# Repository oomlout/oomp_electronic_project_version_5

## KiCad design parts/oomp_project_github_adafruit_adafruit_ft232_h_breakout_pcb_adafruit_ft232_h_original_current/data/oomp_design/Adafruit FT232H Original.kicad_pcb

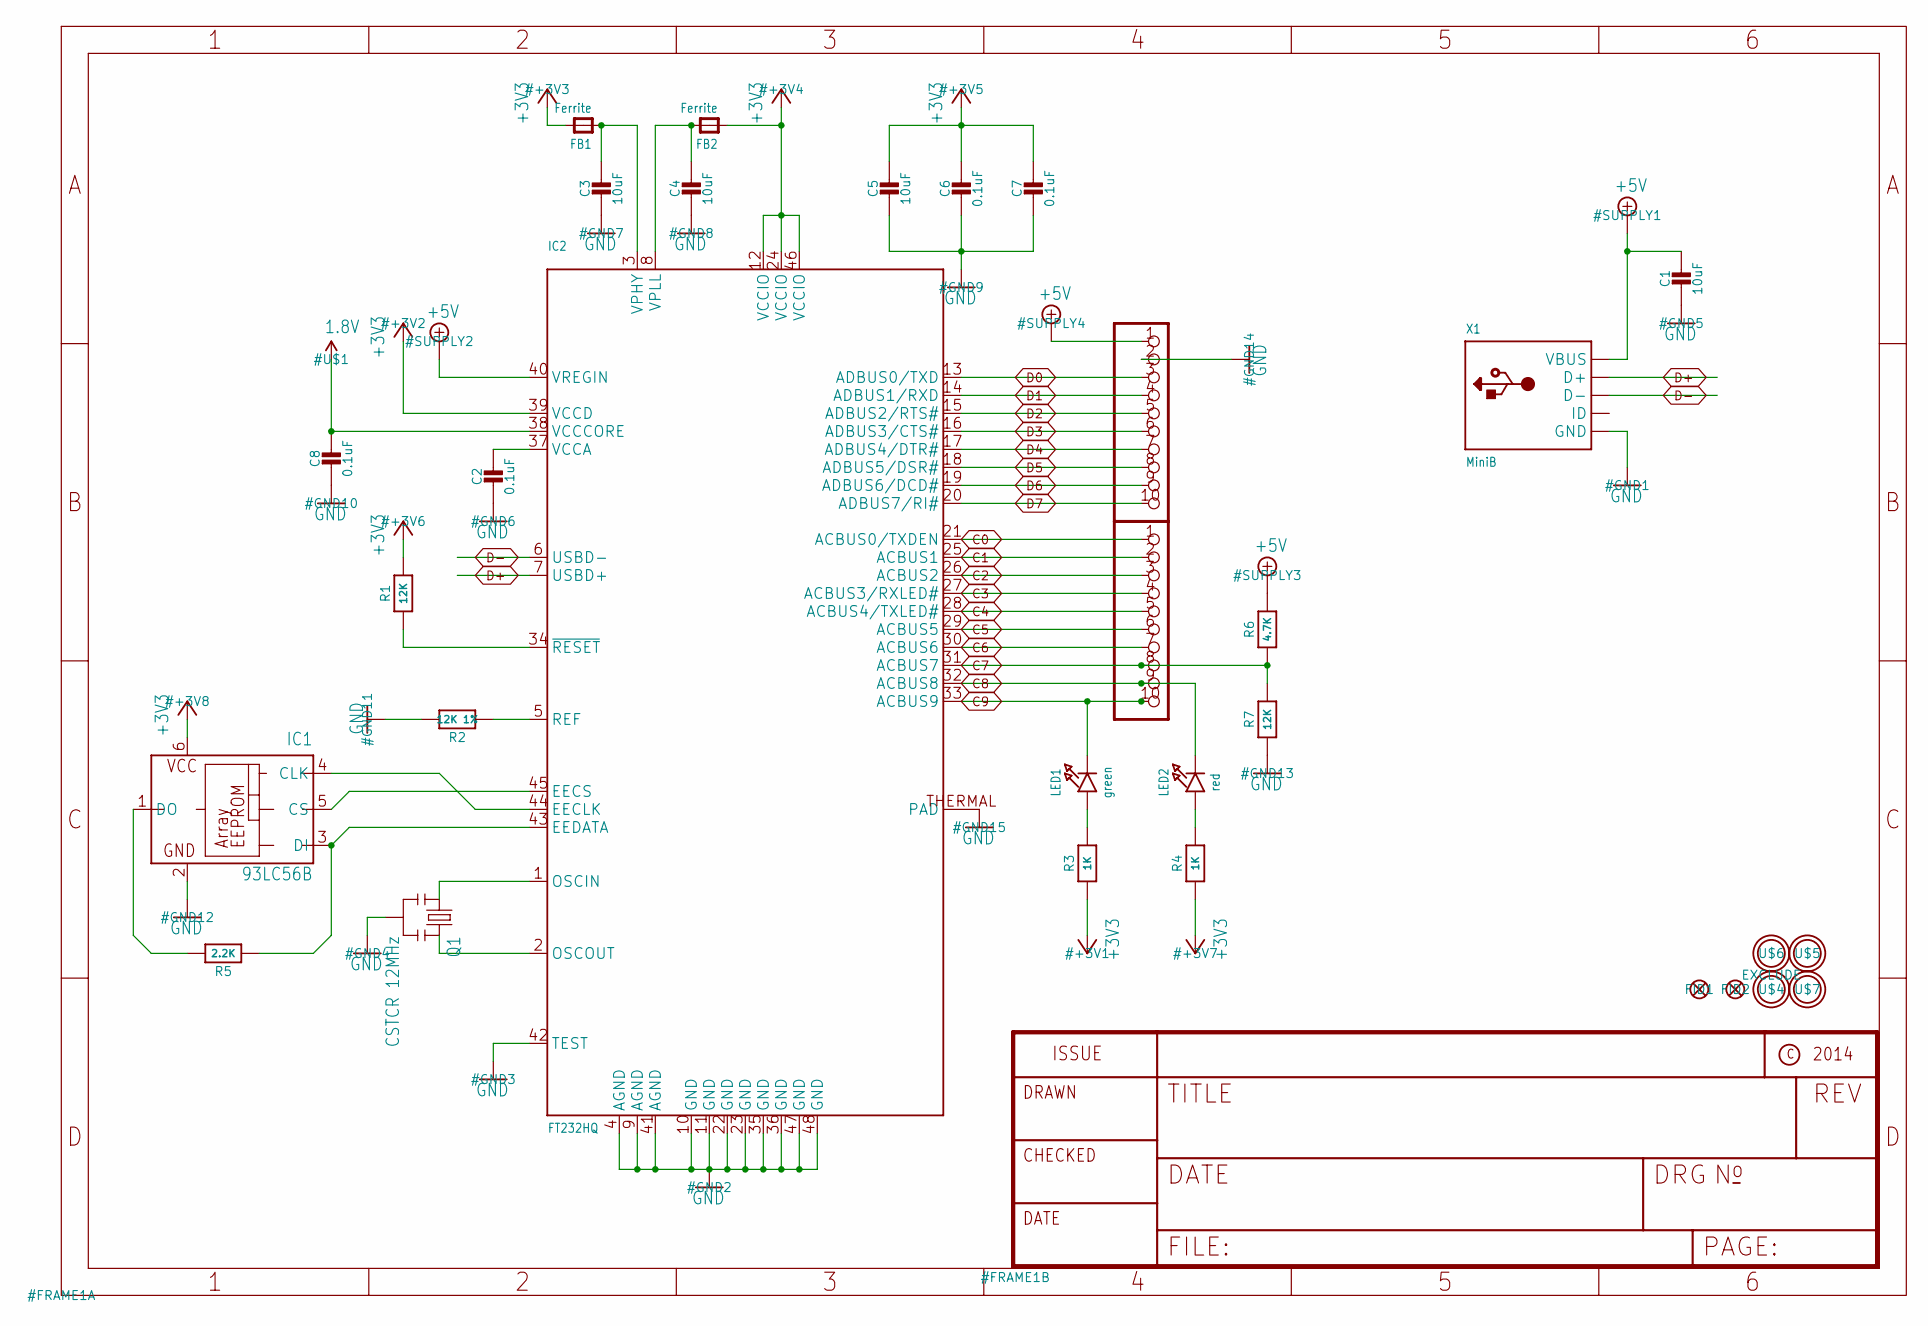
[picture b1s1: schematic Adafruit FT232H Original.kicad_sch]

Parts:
C1, C3, C4, C5: 10uF; 0805-NO
C2, C6, C7, C8: 0.1uF; 0805-NO
FB1, FB2: Ferrite; _0805
FID1, FID2: FIDUCIAL""; FIDUCIAL_1MM
IC1: 93LC56B; SOT23-6; MPN 93LC76AT-I/OT
IC2: FT232HQ; QFN48_8MM
LED1: green; CHIPLED_0805_NOOUTLINE
LED2: red; CHIPLED_0805_NOOUTLINE
Q1: CSTCR 12MHz; RESONATOR-SMD
R1, R7: 12K; 0805-NO
R2: 12K 1%; 0805-NO
R3, R4: 1K; 0805-NO
R5: 2.2K; _0805MP
R6: 4.7K; 0805-NO
U$2, U$3: PINHD-1X10; 1X10-BIG
U$4, U$5, U$6, U$7: MOUNTINGHOLE2.5; MOUNTINGHOLE_2.5_PLATED
X1: MiniB; 4UCONN_20329

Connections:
1.8V: C8.1, IC2.38 (VCCCORE)
+3V3: C5.1, C6.1, C7.1, FB1.2, FB2.1, IC1.6 (VCC), IC2.12 (VCCIO), IC2.24 (VCCIO), IC2.39 (VCCD), IC2.46 (VCCIO), R1.2, R3.1, R4.1
+5V: C1.1, IC2.40 (VREGIN), R6.2, U$2.1, X1.VBUS
C0: IC2.21 (ACBUS0/TXDEN), U$3.1
C1: IC2.25 (ACBUS1), U$3.2
C2: IC2.26 (ACBUS2), U$3.3
C3: IC2.27 (ACBUS3/RXLED#), U$3.4
C4: IC2.28 (ACBUS4/TXLED#), U$3.5
C5: IC2.29 (ACBUS5), U$3.6
C6: IC2.30 (ACBUS6), U$3.7
C7: IC2.31 (ACBUS7), R6.1, R7.2, U$3.8
C8: IC2.32 (ACBUS8), LED2.C, U$3.9
C9: IC2.33 (ACBUS9), LED1.C, U$3.10
D0: IC2.13 (ADBUS0/TXD), U$2.3
D1: IC2.14 (ADBUS1/RXD), U$2.4
D2: IC2.15 (ADBUS2/RTS#), U$2.5
D3: IC2.16 (ADBUS3/CTS#), U$2.6
D4: IC2.17 (ADBUS4/DTR#), U$2.7
D5: IC2.18 (ADBUS5/DSR#), U$2.8
D6: IC2.19 (ADBUS6/DCD#), U$2.9
D7: IC2.20 (ADBUS7/RI#), U$2.10
D+: IC2.7 (USBD+), X1.D+
D-: IC2.6 (USBD-), X1.D-
GND: C1.2, C2.2, C3.2, C4.2, C5.2, C6.2, C7.2, C8.2, IC1.2 (GND), IC2.4 (AGND), IC2.9 (AGND), IC2.10 (GND), IC2.11 (GND), IC2.22 (GND), IC2.23 (GND), IC2.35 (GND), IC2.36 (GND), IC2.41 (AGND), IC2.42 (TEST), IC2.47 (GND), IC2.48 (GND), IC2.THERMAL (PAD), Q1.2, R2.2, R7.1, U$2.2, X1.BASE@1 (GND), X1.BASE@2 (GND), X1.GND, X1.SPRT@1 (GND), X1.SPRT@2 (GND), X1.SPRT@3 (GND), X1.SPRT@4 (GND)
unnamed: IC2.1 (OSCIN), Q1.1
unnamed: IC2.2 (OSCOUT), Q1.3
unnamed: IC2.5 (REF), R2.1
unnamed: LED2.A, R4.2
unnamed: IC2.34 (~RESET), R1.1
unnamed: LED1.A, R3.2
unnamed: IC1.3 (DI), IC2.43 (EEDATA), R5.1
unnamed: IC1.5 (CS), IC2.45 (EECS)
unnamed: IC1.4 (CLK), IC2.44 (EECLK)
unnamed: IC1.1 (DO), R5.2
VCCA: C2.1, IC2.37 (VCCA)
VPHY: C3.1, FB1.1, IC2.3 (VPHY)
VPLL: C4.1, FB2.2, IC2.8 (VPLL)

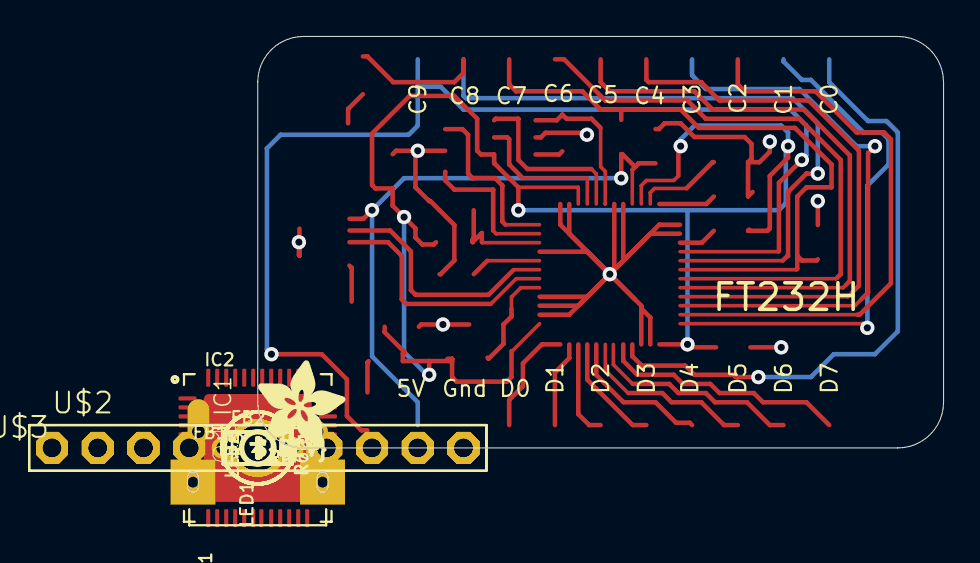
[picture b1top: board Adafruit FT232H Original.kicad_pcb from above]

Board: 2 copper layers, 38.1 x 22.9 mm, 34 parts (1 on the bottom side), 37 nets.

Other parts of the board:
U$8: ADAFRUIT_5MM
U$9: ADAFRUIT_TEXT_30MM
U$11: PCBFEAT-REV-040

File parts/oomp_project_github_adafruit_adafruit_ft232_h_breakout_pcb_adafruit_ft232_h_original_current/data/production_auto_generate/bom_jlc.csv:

Comment,Designator,Footprint,LCSC Part #
,U$8,Adafruit FT232H Original-import-fps:ADAFRUIT_5MM,
,U$9,Adafruit FT232H Original-import-fps:ADAFRUIT_TEXT_30MM,
,U$11,Adafruit FT232H Original-import-fps:PCBFEAT-REV-040,
0.1uF,"C2,C6,C7,C8",Adafruit FT232H Original-import-fps:0805-NO,
10uF,"C1,C3,C4,C5",Adafruit FT232H Original-import-fps:0805-NO,
12K,"R1,R7",Adafruit FT232H Original-import-fps:0805-NO,C2907225
12K 1%,R2,Adafruit FT232H Original-import-fps:0805-NO,C2907225
1K,"R3,R4",Adafruit FT232H Original-import-fps:0805-NO,C17513
2.2K,R5,Adafruit FT232H Original-import-fps:_0805MP,C17520
4.7K,R6,Adafruit FT232H Original-import-fps:0805-NO,C2907264
93LC56B,IC1,Adafruit FT232H Original-import-fps:SOT23-6,
CSTCR 12MHz,Q1,Adafruit FT232H Original-import-fps:RESONATOR-SMD,
Ferrite,"FB1,FB2",Adafruit FT232H Original-import-fps:_0805,
FT232HQ,IC2,Adafruit FT232H Original-import-fps:QFN48_8MM,
green,LED1,Adafruit FT232H Original-import-fps:CHIPLED_0805_NOOUTLINE,
MiniB,X1,Adafruit FT232H Original-import-fps:4UCONN_20329,
PINHD-1X10,"U$2,U$3",Adafruit FT232H Original-import-fps:1X10-BIG,
red,LED2,Adafruit FT232H Original-import-fps:CHIPLED_0805_NOOUTLINE,

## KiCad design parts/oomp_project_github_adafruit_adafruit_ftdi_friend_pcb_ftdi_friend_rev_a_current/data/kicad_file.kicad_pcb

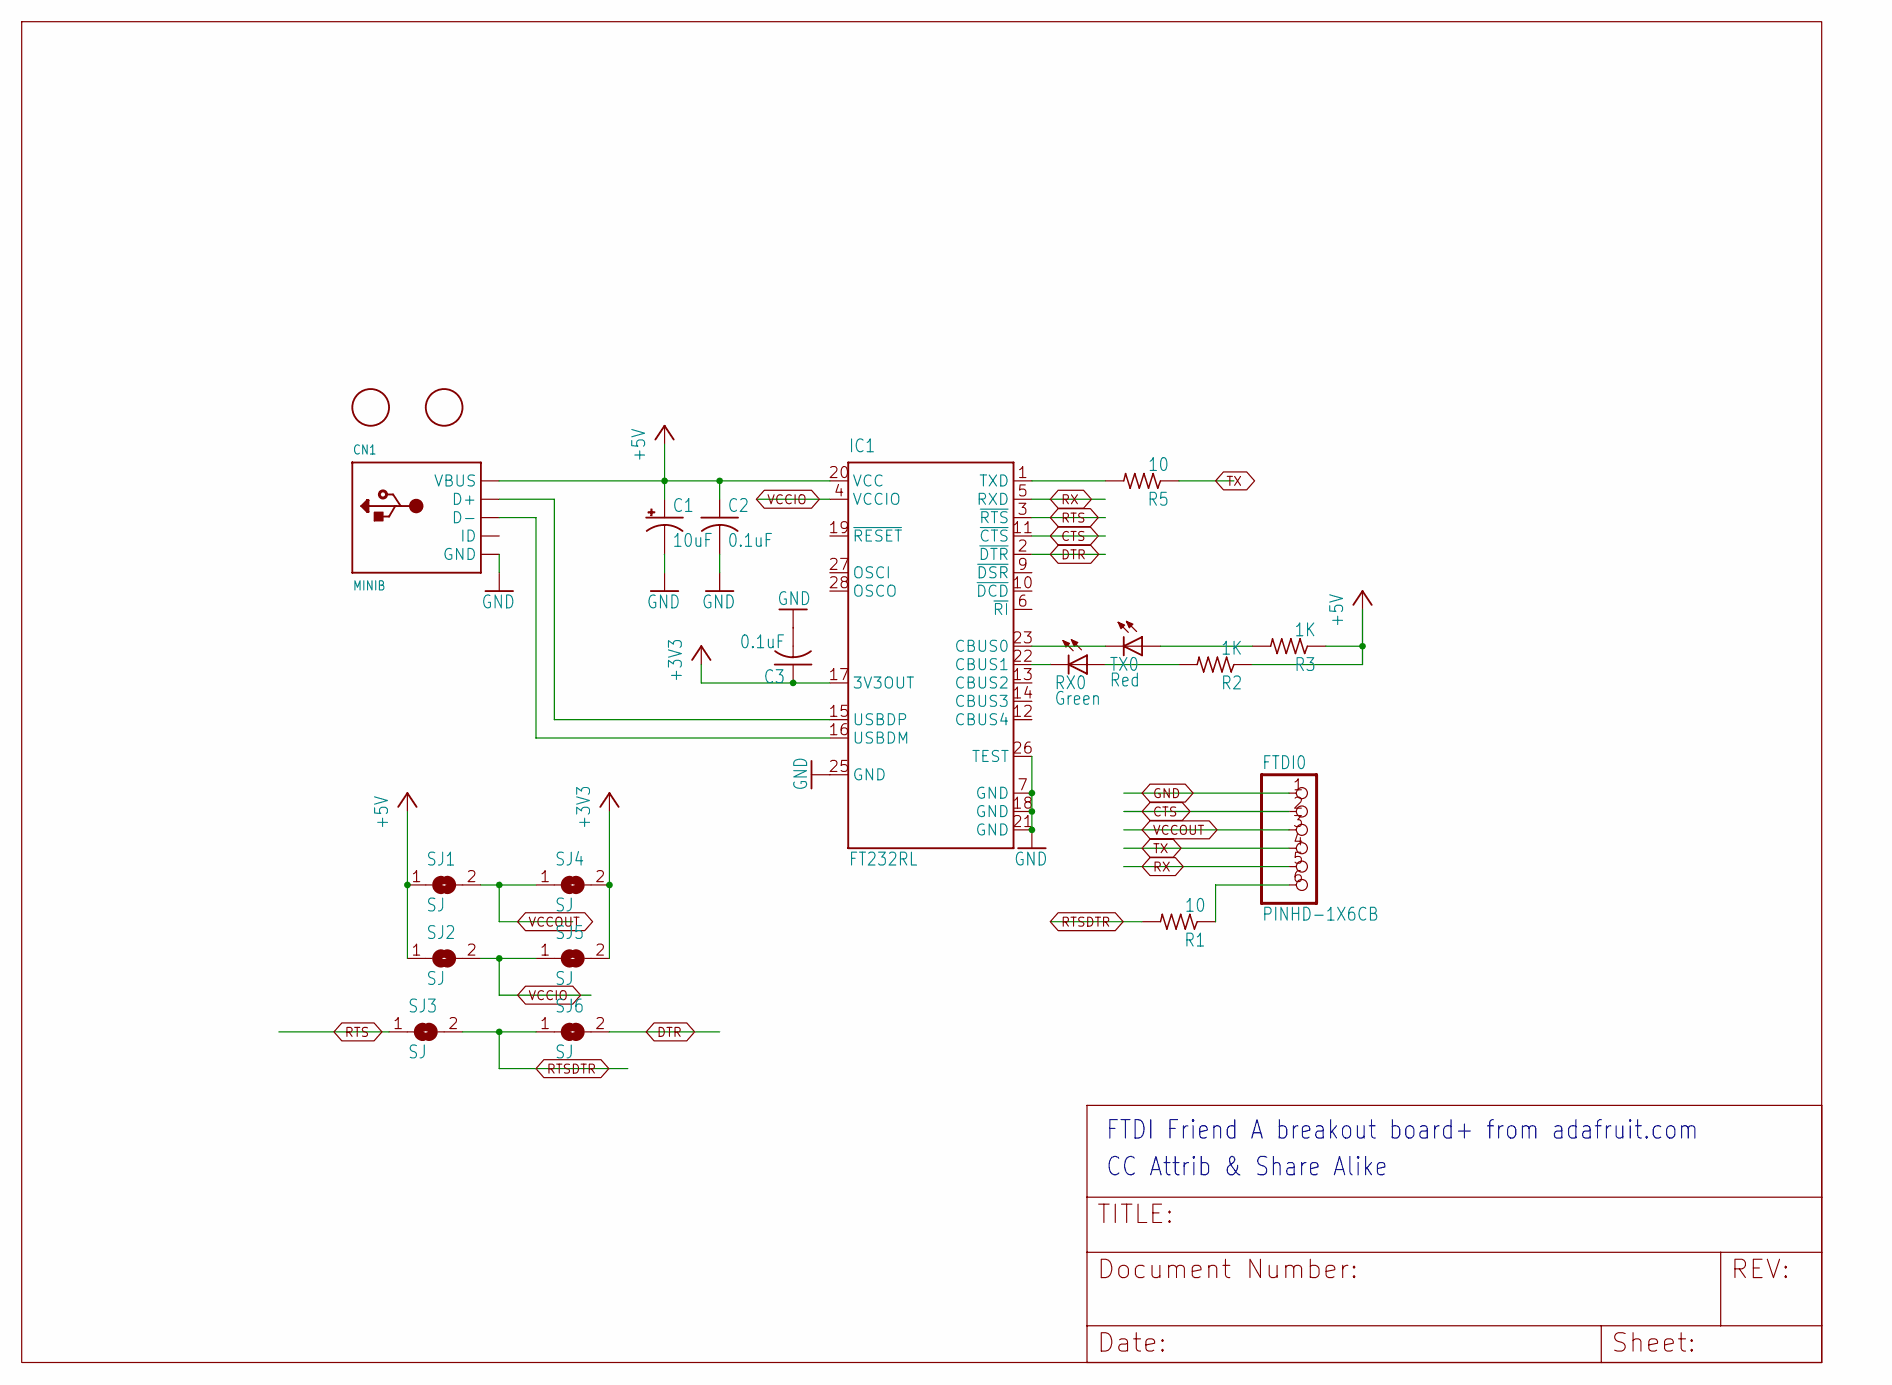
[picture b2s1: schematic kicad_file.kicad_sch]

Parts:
C1: 10uF; A_3216-18R
C2, C3: 0.1uF; C0805K
CN1: MINIB; USB-MINIB
FTDI0: PINHD-1X6CB; 1X06-CLEANBIG
IC1: FT232RL; SSOP28
R1, R5: 10; R0805
R2, R3: 1K; R0805
RX0: Green; CHIP-LED0805
SJ1, SJ2, SJ3, SJ4, SJ5, SJ6: SJ
TX0: Red; CHIP-LED0805
U$1, U$2: FIDUCIAL; FIDUCIAL_1MM

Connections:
+3V3: C3.1, IC1.17 (3V3OUT), SJ4.2, SJ5.2
+5V: C1.+, C2.1, CN1.VBUS, IC1.20 (VCC), R2.1, R3.1, SJ1.1, SJ2.1
CTS: FTDI0.2, IC1.11 (~CTS)
DTR: IC1.2 (~DTR), SJ6.2
GND: C1.-, C2.2, C3.2, CN1.GND, FTDI0.1, IC1.7 (GND), IC1.18 (GND), IC1.21 (GND), IC1.25 (GND), IC1.26 (TEST)
unnamed: FTDI0.6, R1.1
unnamed: CN1.D+, IC1.15 (USBDP)
unnamed: CN1.D-, IC1.16 (USBDM)
unnamed: IC1.1 (TXD), R5.2
unnamed: IC1.23 (CBUS0), TX0.C
unnamed: IC1.22 (CBUS1), RX0.C
unnamed: R2.2, RX0.A
unnamed: R3.2, TX0.A
RTS: IC1.3 (~RTS), SJ3.1
RTSDTR: R1.2, SJ3.2, SJ6.1
RX: FTDI0.5, IC1.5 (RXD)
TX: FTDI0.4, R5.1
VCCIO: IC1.4 (VCCIO), SJ2.2, SJ5.1
VCCOUT: FTDI0.3, SJ1.2, SJ4.1

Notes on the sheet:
CC Attrib & Share Alike
FTDI Friend~{} A breakout board+ from adafruit.com

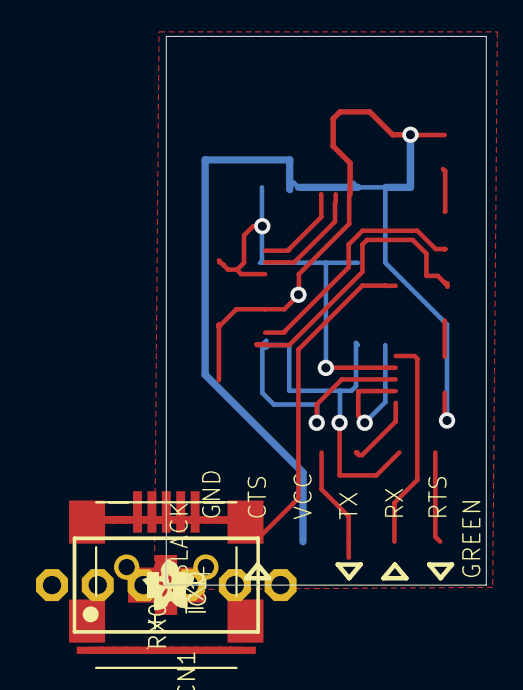
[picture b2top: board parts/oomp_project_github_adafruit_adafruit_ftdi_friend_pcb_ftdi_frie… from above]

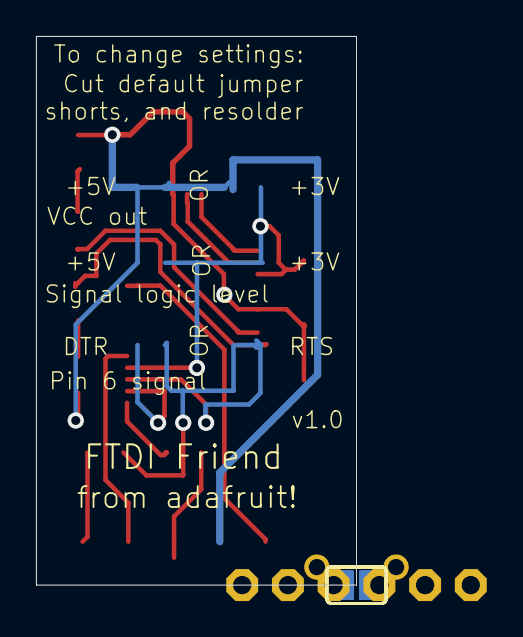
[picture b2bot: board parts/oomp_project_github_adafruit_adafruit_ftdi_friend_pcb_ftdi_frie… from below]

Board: 16 copper layers, 17.8 x 30.5 mm, 21 parts (6 on the bottom side), 19 nets.

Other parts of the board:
U$3: ADAFRUIT200MIL

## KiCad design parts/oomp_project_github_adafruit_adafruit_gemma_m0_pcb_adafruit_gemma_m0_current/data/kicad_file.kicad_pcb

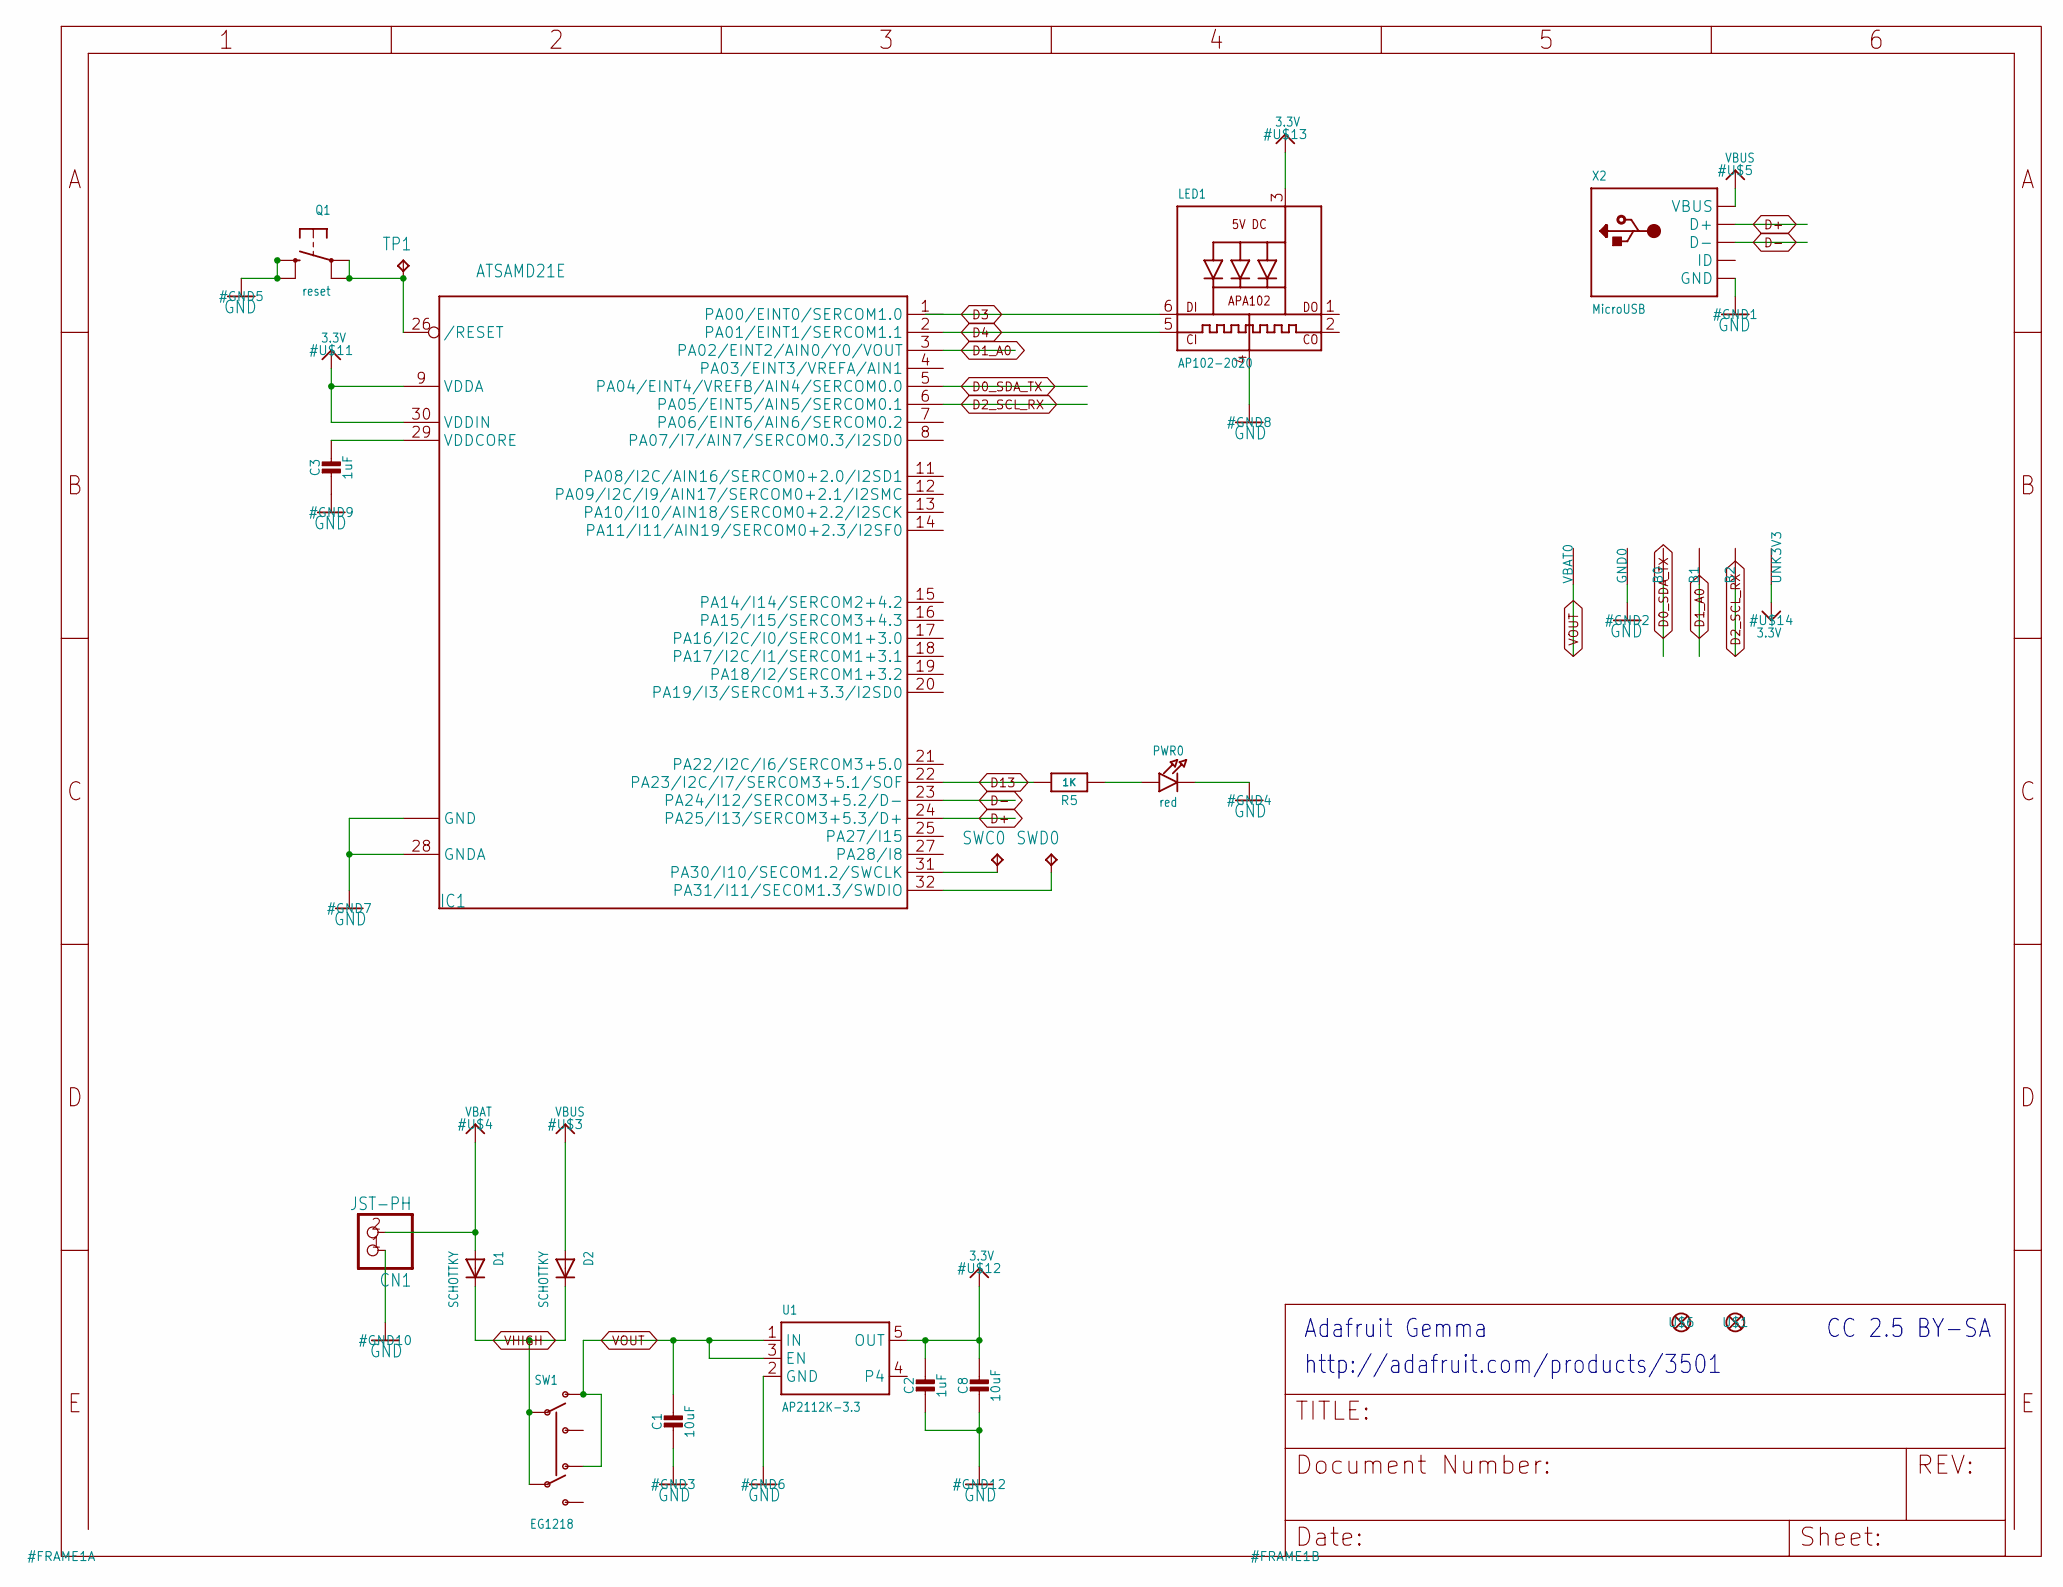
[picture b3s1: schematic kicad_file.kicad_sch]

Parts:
B0, B1, B2: SEWTAP-ALLIGATOR; SEWALLI
C1, C8: 10uF; 0805-NO
C2, C3: 1uF; 0603-NO
CN1: JST-PH; JSTPH2
D1, D2: SCHOTTKY; SOD-123FL
GND0: SEWTAP-ALLIGATOR; SEWALLI
IC1: ATSAMD21E; QFN32_5MM
LED1: AP102-2020; APA102_2020
PWR0: red; CHIPLED_0603_NOOUTLINE
Q1: reset; BTN_KMR2_4.6X2.8
R5: 1K; 0603-NO
SW1: EG1218; EG1390
SWC0: TPTP15R; TP15R
SWD0: TPTP15R; TP15R
TP1: TPTP16R; TP16R
U1: AP2112K-3.3; SOT23-5
U$1, U$6: FIDUCIAL_1MM
UNK3V3: SEWTAP-ALLIGATOR; SEWALLI
VBAT0: SEWTAP-ALLIGATOR; SEWALLI
X2: MicroUSB; 4UCONN_20329_V2

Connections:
3.3V: C2.1, C8.1, IC1.9 (VDDA), IC1.30 (VDDIN), LED1.3 (VDD), U1.5 (OUT), UNK3V3.P$1
D0_SDA_TX: B0.P$1, IC1.5 (PA04/EINT4/VREFB/AIN4/SERCOM0.0)
D1_A0: B1.P$1, IC1.3 (PA02/EINT2/AIN0/Y0/VOUT)
D2_SCL_RX: B2.P$1, IC1.6 (PA05/EINT5/AIN5/SERCOM0.1)
D3: IC1.1 (PA00/EINT0/SERCOM1.0), LED1.6 (DI)
D4: IC1.2 (PA01/EINT1/SERCOM1.1), LED1.5 (CKI)
D13: IC1.22 (PA23/I2C/I7/SERCOM3+5.1/SOF), R5.2
D+: IC1.24 (PA25/I13/SERCOM3+5.3/D+), X2.D+
D-: IC1.23 (PA24/I12/SERCOM3+5.2/D-), X2.D-
GND: C1.2, C2.2, C3.2, C8.2, CN1.1, GND0.P$1, IC1.10 (GND), IC1.28 (GNDA), IC1.33 (GND), LED1.4 (GND), PWR0.C, Q1.B (S), Q1.B' (S1), U1.2 (GND), X2.BASE@1 (GND), X2.BASE@2 (GND), X2.GND, X2.SPRT@1 (GND), X2.SPRT@2 (GND), X2.SPRT@3 (GND), X2.SPRT@4 (GND)
unnamed: PWR0.A, R5.1
SWCLK: IC1.31 (PA30/I10/SECOM1.2/SWCLK), SWC0.TP
SWDIO: IC1.32 (PA31/I11/SECOM1.3/SWDIO), SWD0.TP
VBAT: CN1.2, D1.A
VBUS: D2.A, X2.VBUS
VDDCORE: C3.1, IC1.29 (VDDCORE)
VHIGH: D1.C, D2.C, SW1.P1, SW1.P2
VOUT: C1.1, SW1.O1, SW1.O2, U1.1 (IN), U1.3 (EN), VBAT0.P$1
~RESET: IC1.26 (/RESET), Q1.A, Q1.A' (P1), TP1.TP

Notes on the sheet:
Adafruit Gemma
CC 2.5 BY-SA
http://adafruit.com/products/3501

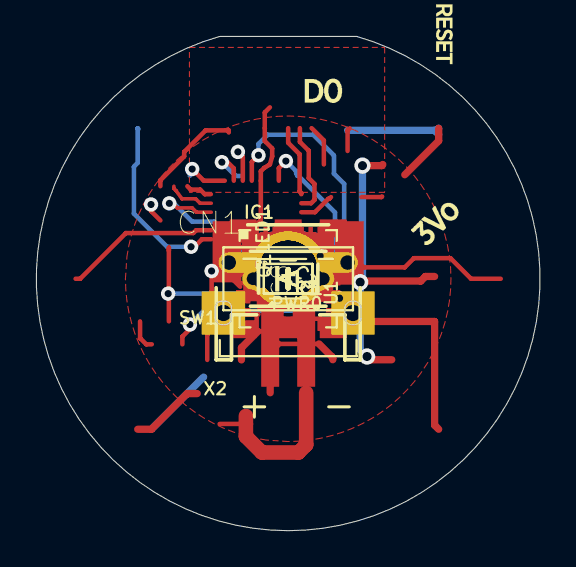
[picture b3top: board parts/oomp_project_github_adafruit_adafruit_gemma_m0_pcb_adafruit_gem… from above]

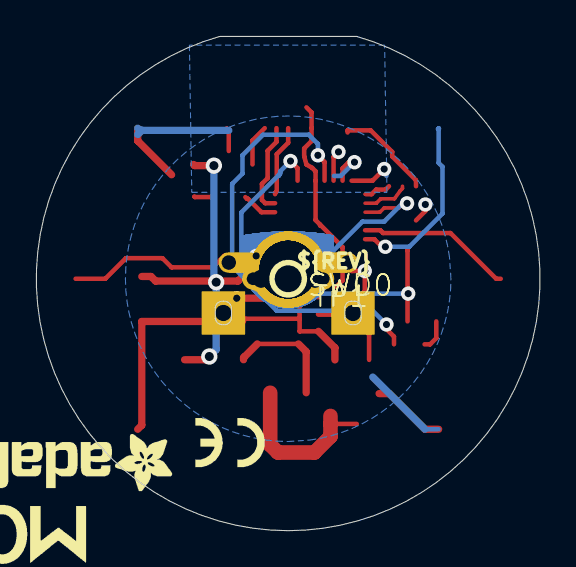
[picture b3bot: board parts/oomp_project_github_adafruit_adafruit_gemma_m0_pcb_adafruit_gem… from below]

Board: 16 copper layers, 28.0 x 27.5 mm, 29 parts (5 on the bottom side), 19 nets.

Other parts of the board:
U$7: GEMMA_M0_BOTTOM
U$8: GEMMA_M0_TOP
U$10: PCBFEAT-REV-040

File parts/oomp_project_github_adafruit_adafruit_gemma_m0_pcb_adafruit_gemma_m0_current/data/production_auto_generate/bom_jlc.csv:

Comment,Designator,Footprint,LCSC Part #
,U$7,Adafruit Gemma M0-import-fps:GEMMA_M0_BOTTOM,
,U$8,Adafruit Gemma M0-import-fps:GEMMA_M0_TOP,
,U$10,Adafruit Gemma M0-import-fps:PCBFEAT-REV-040,
10uF,"C1,C8",Adafruit Gemma M0-import-fps:0805-NO,
1K,R5,Adafruit Gemma M0-import-fps:0603-NO,C2907002
1uF,"C2,C3",Adafruit Gemma M0-import-fps:0603-NO,C5673
AP102-2020,LED1,Adafruit Gemma M0-import-fps:APA102_2020,
AP2112K-3.3,U1,Adafruit Gemma M0-import-fps:SOT23-5,
ATSAMD21E,IC1,Adafruit Gemma M0-import-fps:QFN32_5MM,
EG1218,SW1,Adafruit Gemma M0-import-fps:EG1390,
FIDUCIAL_1MM,"U$1,U$6",Adafruit Gemma M0-import-fps:FIDUCIAL_1MM,
JST-PH,CN1,Adafruit Gemma M0-import-fps:JSTPH2,
MicroUSB,X2,Adafruit Gemma M0-import-fps:4UCONN_20329_V2,
red,PWR0,Adafruit Gemma M0-import-fps:CHIPLED_0603_NOOUTLINE,
reset,Q1,Adafruit Gemma M0-import-fps:BTN_KMR2_4.6X2.8,
SCHOTTKY,"D1,D2",Adafruit Gemma M0-import-fps:SOD-123FL,
TPTP15R,"SWC0,SWD0",Adafruit Gemma M0-import-fps:TP15R,
TPTP16R,TP1,Adafruit Gemma M0-import-fps:TP16R,
